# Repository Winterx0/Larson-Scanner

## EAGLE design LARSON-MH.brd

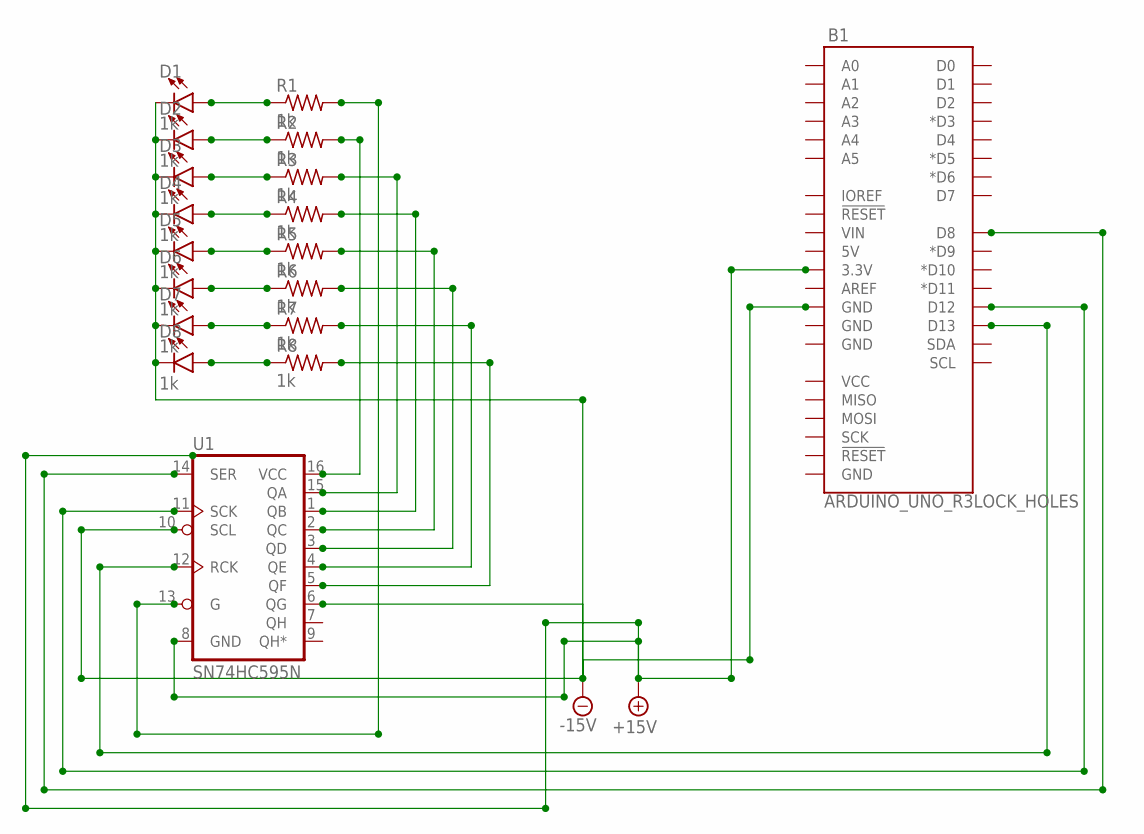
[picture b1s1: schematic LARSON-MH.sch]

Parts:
B1: ARDUINO_UNO_R3LOCK_HOLES; ARDUINO_R3_LOCK_HOLES
D1, D2, D3, D4, D5, D6, D7, D8: 1k; LED_5MM
R1, R2, R3, R4, R5, R6, R7, R8: 1k; R0603
U1: SN74HC595N; DIP16

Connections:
+15V: B1.3.3V, U1.8 (GND)
-15V: B1.GND@4 (GND), D1.K (C), D2.K (C), D3.K (C), D4.K (C), D5.K (C), D6.K (C), D7.K (C), D8.K (C), U1.6 (QG), U1.10 (SCL)
unnamed: B1.D13, U1.12 (RCK)
unnamed: R3.2, U1.15 (QA)
unnamed: D1.A, R1.1
unnamed: D2.A, R2.1
unnamed: D3.A, R3.1
unnamed: D4.A, R4.1
unnamed: D5.A, R5.1
unnamed: D6.A, R6.1
unnamed: D7.A, R7.1
unnamed: D8.A, R8.1
unnamed: R1.2, U1.13 (G)
unnamed: R4.2, U1.1 (QB)
unnamed: B1.D12, U1.11 (SCK)
unnamed: B1.D8, U1.14 (SER)
unnamed: R5.2, U1.2 (QC)
unnamed: R2.2, U1.16 (VCC)
unnamed: R6.2, U1.3 (QD)
unnamed: R7.2, U1.4 (QE)
unnamed: R8.2, U1.5 (QF)

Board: 2 copper layers, 18 parts (0 on the bottom side), 21 nets, no tracks yet.

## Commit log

2023-04-06 Larson Scanner Docs
    Schematic
    Board Print Layout
    Code

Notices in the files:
parts and their libraries:
SparkFun-Boards: Licensing: Creative Commons ShareAlike 4.0 International - https://creativecommons.org/licenses/by-sa/4.0
